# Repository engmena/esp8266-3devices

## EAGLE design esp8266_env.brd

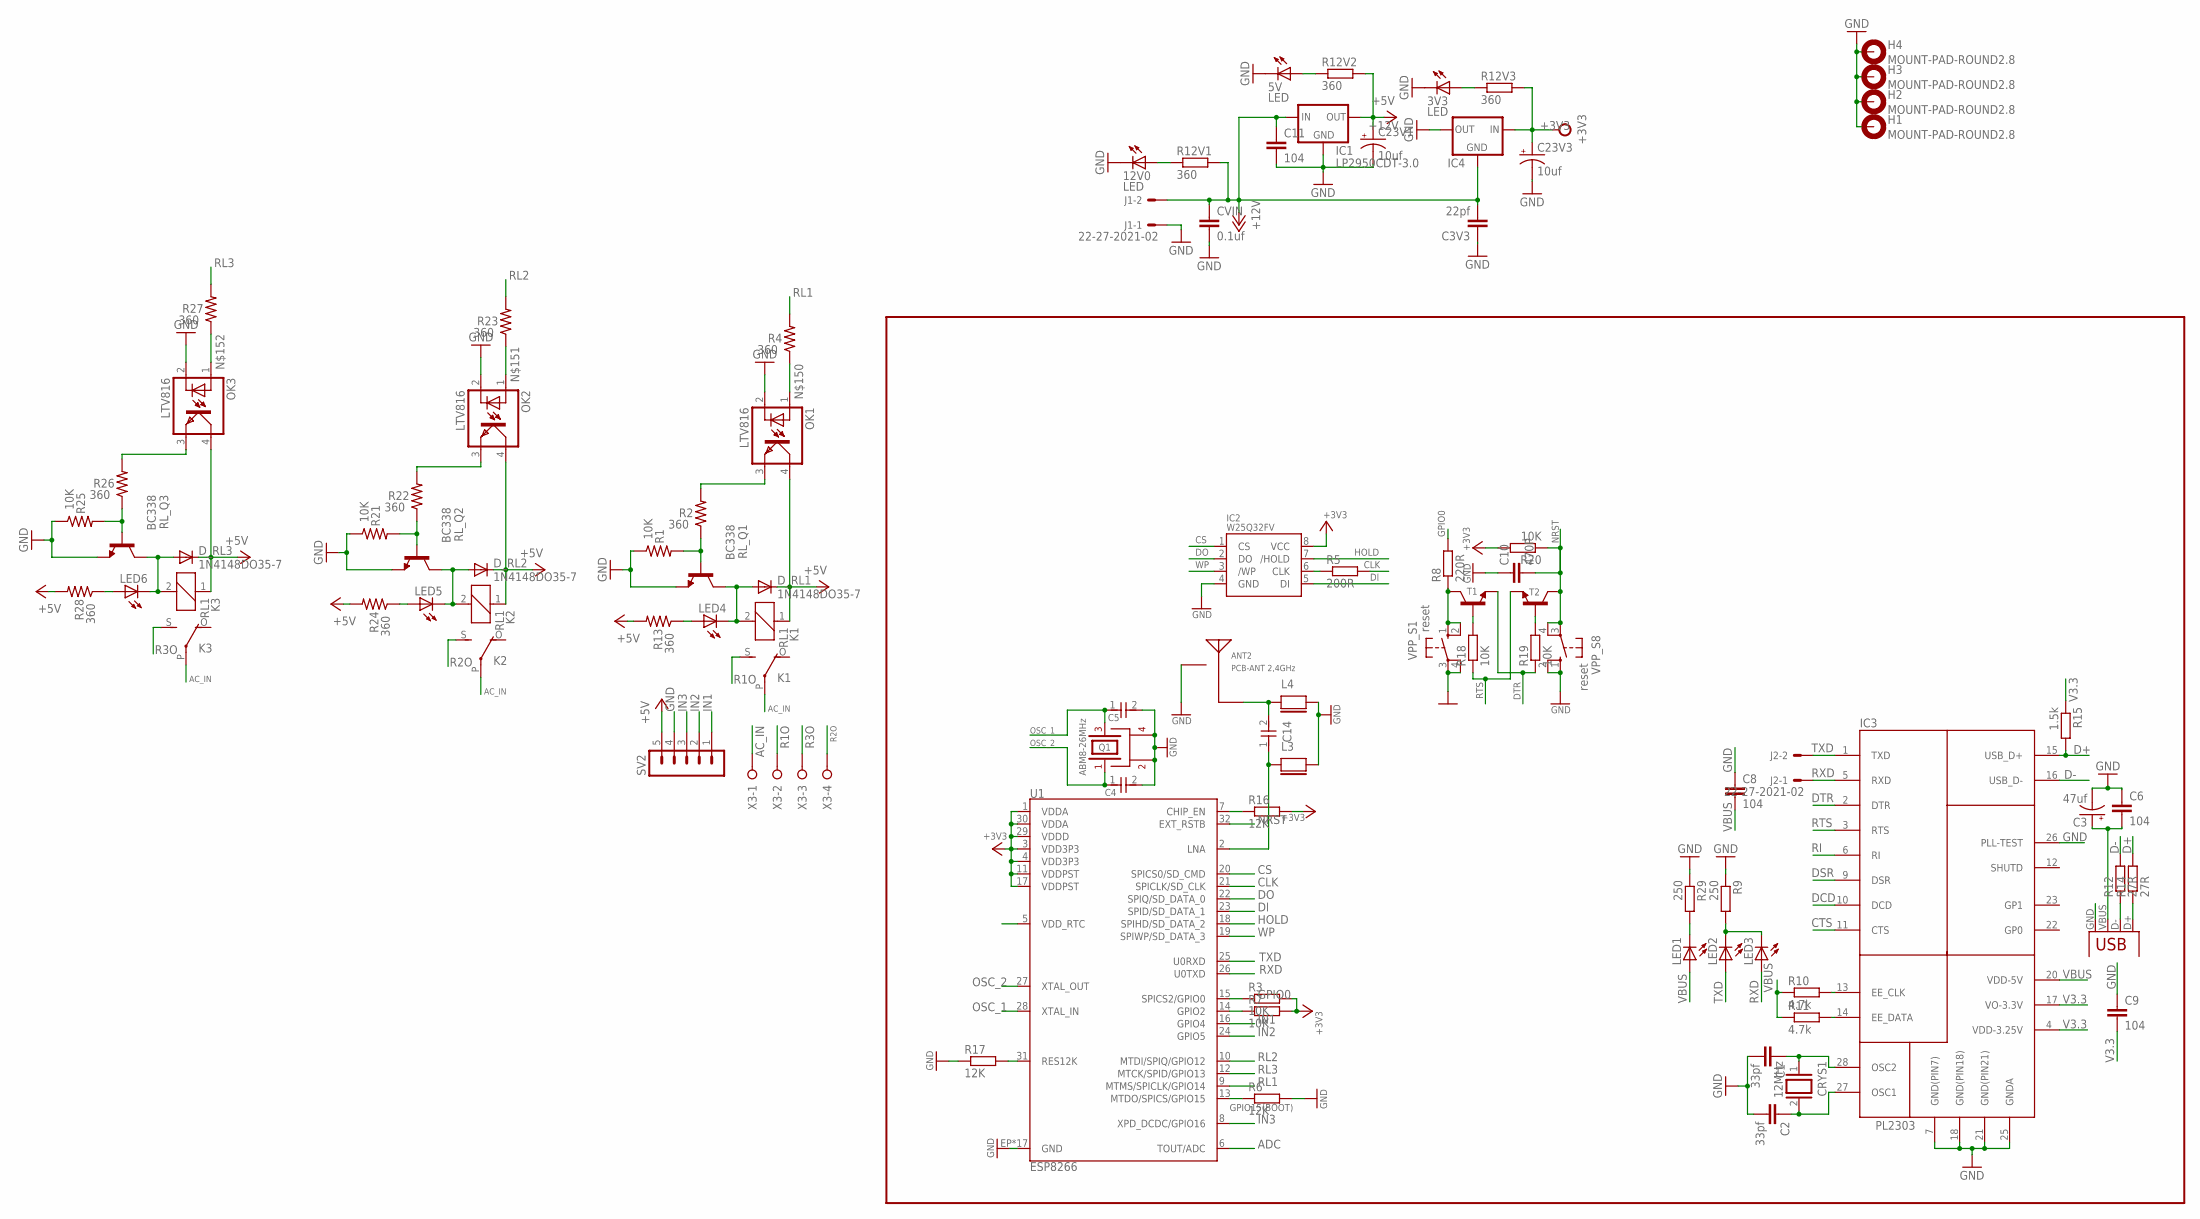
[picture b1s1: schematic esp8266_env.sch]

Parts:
3V3, 5V, 12V0: LED; SML0805
ANT2: PCB-ANT 2,4GHz; 2.4GHZ_PCB
C1, C2: 33pf; C0805
C3: 47uf; E2,5-5
C3V3: 22pf; C0805
C4, C5: 10P-50VCOG_0603; C0603
C6, C8, C9, C11: 104; C0805
C10: 470P; C0805
C14: 5.6pF; C0402
C23V1, C23V3: 10uf; E2,5-5
CRYS1: 12MHz; QS
CVIN: 0.1uf; C0805
D_RL1, D_RL2, D_RL3: 1N4148DO35-7; DO35-7
H1, H2, H3, H4: MOUNT-PAD-ROUND2.8; 2,8-PAD
IC1: LP2950CDT-3.0; DPACK
IC2: W25Q32FV; SOIC-8_208MIL
IC3: PL2303; SSOP28
IC4: LM1117; SOT223
J1, J2: 22-27-2021-02; 6410-02
K1, K2, K3: RL1; G5LE
L3, L4: NC; L0402
LED1, LED2, LED3, LED4, LED5, LED6: LEDSML0805; SML0805
OK1, OK2, OK3: LTV816; DIL04
Q1: ABM8-26MHz; ABM8G
R1, R21, R25: 10K; 0805
R2, R4, R13, R22, R23, R24, R26, R27, R28: 360; 0805
R3, R7, R18, R19, R20: 10K; M0805
R5: 200R; M0805
R6, R16, R17: 12K; M0805
R8: 220R; M0805
R9, R29: 250; R0805
R10, R11: 4.7k; M0805
R12, R14: 27R; R0805
R12V1, R12V2, R12V3: 360; R0805
R15: 1.5k; R0805
RL_Q1, RL_Q2, RL_Q3: BC338; TO92-EBC
SV2: MA05-1
T1, T2: BC817-NPN-SOT23-BEC; SOT23-BEC
U1: ESP8266; QFN32-5X5MM
VPP_S1, VPP_S8: reset; B3F-10XX
X1: USB-MICROB
X3: W237-04P; W237-4P

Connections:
+3V3: C23V3.+, IC2.8 (VCC), IC4.3 (IN), R3.2, R7.2, R12V3.2, R16.2, R20.2, U1.1 (VDDA), U1.3 (VDD3P3), U1.4 (VDD3P3), U1.11 (VDDPST), U1.17 (VDDPST), U1.29 (VDDD), U1.30 (VDDA)
+5V: C23V1.+, D_RL1.C, D_RL2.C, D_RL3.C, IC1.3 (OUT), K1.1, K2.1, K3.1, OK1.4 (COL), OK2.4 (COL), OK3.4 (COL), R12V2.2, R13.2, R24.2, R28.2, SV2.5
+12V: C3V3.2, C11.1, CVIN.1, IC1.1 (IN), IC4.1 (GND), J1.2, R12V1.2
AC_IN: K1.P, K2.P, K3.P, X3.1
ADC: U1.6 (TOUT/ADC)
CLK: R5.2, U1.21 (SPICLK/SD_CLK)
CS: IC2.1 (CS), U1.20 (SPICS0/SD_CMD)
CTS: IC3.11 (CTS)
D+: IC3.15 (USB_D+), R14.2, R15.2
D-: IC3.16 (USB_D-), R12.2
DCD: IC3.10 (DCD)
DI: IC2.5 (DI), U1.23 (SPID/SD_DATA_1)
DO: IC2.2 (DO), U1.22 (SPIQ/SD_DATA_0)
DSR: IC3.9 (DSR)
DTR: IC3.2 (DTR), R19.1, T1.E
GND: 3V3.C, 5V.C, 12V0.C, ANT2.GND (2), C1.2, C2.2, C3.-, C3V3.1, C4.2, C5.2, C6.1, C8.1, C9.1, C10.1, C11.2, C23V1.-, C23V3.-, CVIN.2, H1.B2,8, H2.B2,8, H3.B2,8, H4.B2,8, IC1.4 (GND), IC2.4 (GND), IC3.7 (GND(PIN7)), IC3.18 (GND(PIN18)), IC3.21 (GND(PIN21)), IC3.25 (GNDA), IC3.26 (PLL-TEST), IC4.2 (OUT), J1.1, L3.2, L4.2, OK1.2 (C), OK2.2 (C), OK3.2 (C), Q1.2, Q1.4, R1.1, R6.2, R9.1, R17.1, R21.1, R25.1, R29.1, RL_Q1.E, RL_Q2.E, RL_Q3.E, SV2.4, U1.EP (GND), U1.P$1 (GND), U1.P$2 (GND), U1.P$3 (GND), U1.P$4 (GND), U1.P$5 (GND), U1.P$6 (GND), U1.P$7 (GND), U1.P$8 (GND), U1.P$9 (GND), U1.P$10 (GND), U1.P$11 (GND), U1.P$12 (GND), U1.P$13 (GND), U1.P$14 (GND), U1.P$15 (GND), U1.P$16 (GND), VPP_S1.3, VPP_S1.4 (P1), VPP_S8.1 (S), VPP_S8.2 (S1), X1.GND
GPIO0: R3.1, R8.2, U1.15 (SPICS2/GPIO0)
HOLD: IC2.7 (/HOLD), U1.18 (SPIHD/SD_DATA_2)
IN1: SV2.1, U1.16 (GPIO4)
IN2: SV2.2, U1.24 (GPIO5)
IN3: SV2.3, U1.8 (XPD_DCDC/GPIO16)
LNA: C14.1, L3.1, U1.2 (LNA)
unnamed: R19.2, T2.B
unnamed: C2.1, CRYS1.2, IC3.27 (OSC1)
unnamed: R17.2, U1.31 (RES12K)
unnamed: R18.2, T1.B
unnamed: R21.2, R22.1, RL_Q2.B
unnamed: OK2.3 (EMIT), R22.2
unnamed: IC2.6 (CLK), R5.1
unnamed: IC3.13 (EE_CLK), R10.2
unnamed: R1.2, R2.1, RL_Q1.B
unnamed: IC3.14 (EE_DATA), R11.2
unnamed: LED2.C, LED3.C, R9.2
unnamed: R14.1, X1.D+
unnamed: R12.1, X1.D-
unnamed: OK1.3 (EMIT), R2.2
unnamed: R16.1, U1.7 (CHIP_EN)
unnamed: LED4.A, R13.1
unnamed: LED5.A, R24.1
unnamed: R25.2, R26.1, RL_Q3.B
unnamed: OK3.3 (EMIT), R26.2
unnamed: LED6.A, R28.1
unnamed: 5V.A, R12V2.1
unnamed: 3V3.A, R12V3.1
unnamed: ANT2.ANT (1), C14.2, L4.1
unnamed: R7.1, U1.14 (GPIO2)
unnamed: LED1.C, R29.2
unnamed: R8.1, T1.C, VPP_S1.1 (S), VPP_S1.2 (S1)
unnamed: C1.1, CRYS1.1, IC3.28 (OSC2)
unnamed: 12V0.A, R12V1.1
unnamed: OK1.1 (A), R4.1
unnamed: OK2.1 (A), R23.1
unnamed: OK3.1 (A), R27.1
NRST: C10.2, R20.1, T2.C, U1.32 (EXT_RSTB), VPP_S8.3, VPP_S8.4 (P1)
OSC_1: C5.1, Q1.3, U1.28 (XTAL_IN)
OSC_2: C4.1, Q1.1, U1.27 (XTAL_OUT)
R1O: K1.S, X3.2
R2O: K2.S, X3.4
R3O: K3.S, X3.3
RI: IC3.6 (RI)
RL1: R4.2, U1.9 (MTMS/SPICLK/GPIO14)
RL2: R23.2, U1.10 (MTDI/SPIQ/GPIO12)
RL3: R27.2, U1.12 (MTCK/SPID/GPIO13)
RLE1: D_RL1.A, K1.2, LED4.C, RL_Q1.C
RLE2: D_RL2.A, K2.2, LED5.C, RL_Q2.C
RLE3: D_RL3.A, K3.2, LED6.C, RL_Q3.C
RTS: IC3.3 (RTS), R18.1, T2.E
RXD: IC3.5 (RXD), J2.1, LED3.A, U1.26 (U0TXD)
SS1: R6.1, U1.13 (MTDO/SPICS/GPIO15)
TXD: IC3.1 (TXD), J2.2, LED2.A, U1.25 (U0RXD)
V3.3: C9.2, IC3.4 (VDD-3.25V), IC3.17 (VO-3.3V), R15.1
VBUS: C3.+, C6.2, C8.2, IC3.20 (VDD-5V), LED1.A, R10.1, R11.1, X1.VBUS
WP: IC2.3 (/WP), U1.19 (SPIWP/SD_DATA_3)

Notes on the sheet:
GPIO15(BOOT)

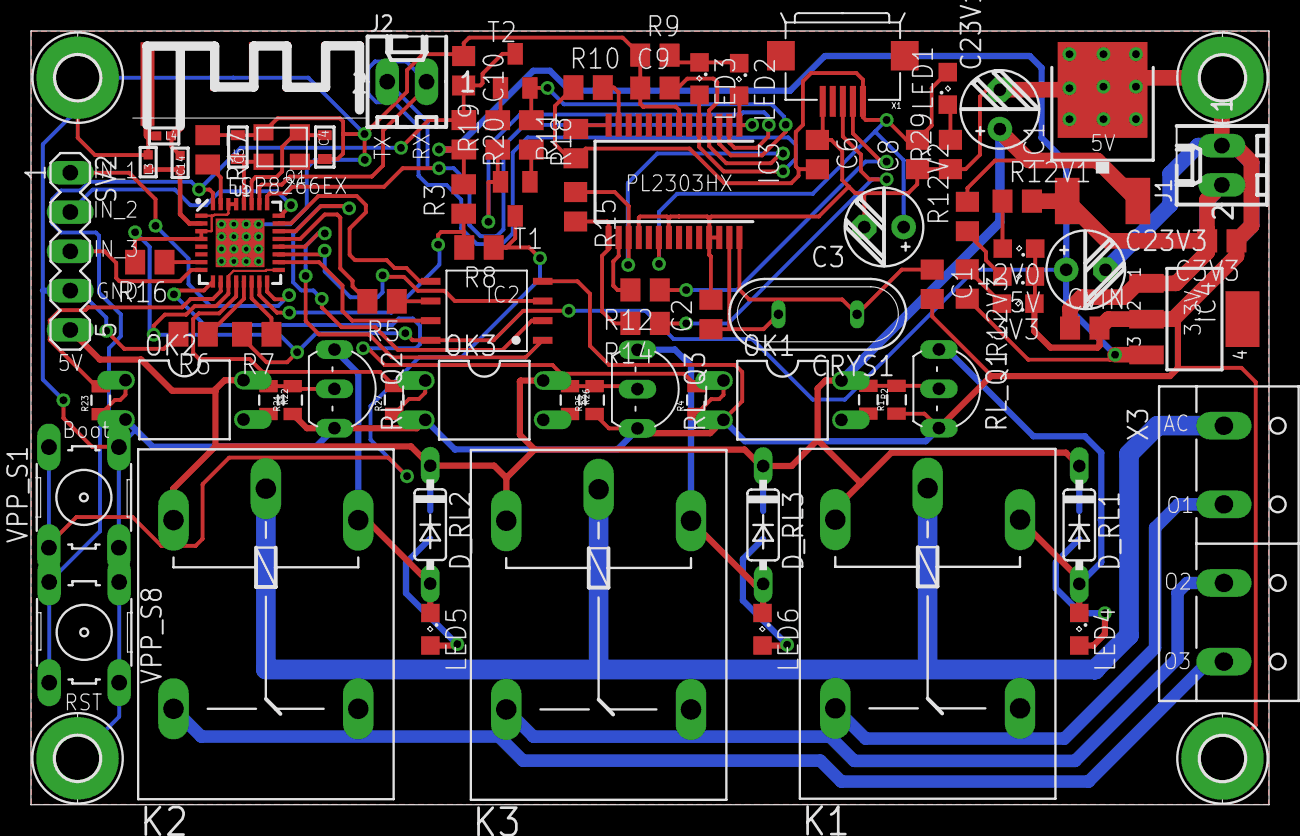
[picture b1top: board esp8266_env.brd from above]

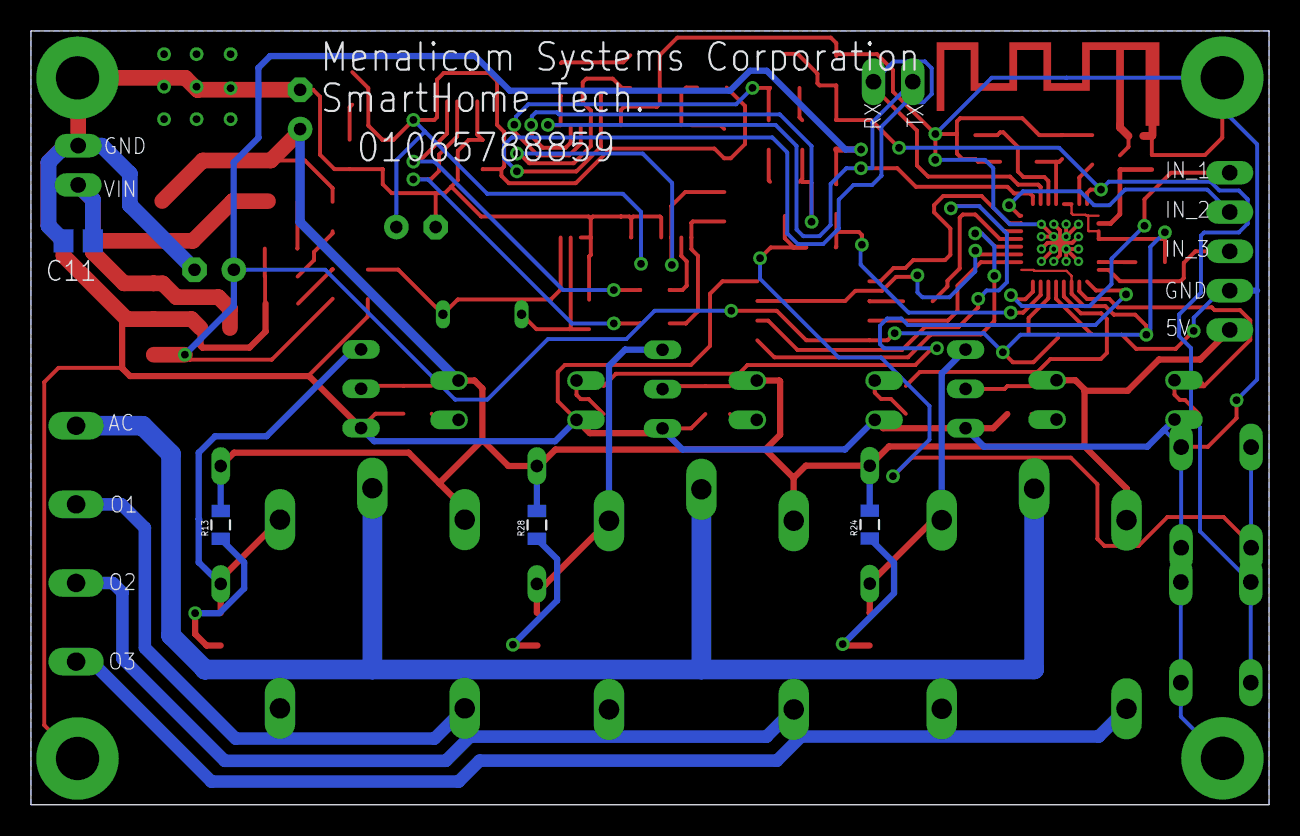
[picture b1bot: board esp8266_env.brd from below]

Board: 2 copper layers, 80.0 x 50.0 mm, 91 parts (4 on the bottom side), 68 nets.

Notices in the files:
parts and their libraries:
SparkFun-Resistors: Licensing: CC v3.0 Share-Alike You are welcome to use this library for commercial purposes.
